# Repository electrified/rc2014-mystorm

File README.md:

## Board to interface 3.3v FPGA board with RC2014

BOM

5x SN74LVCC3245ADW

LD1117S33TR

100nF 0805 capacitors

10μF 0805 capacitors

OE low = enable
dir rc ->fpga

objcopy -Iihex -Obinary nascom32k_hexloadr.hex out.bin

sigrok-cli --driver saleae-logic16 --config samplerate=20Mhz --channels 0=D0,1=D1,2=D2,3=D3,4=D4,5=D5,6=D6,7=D7,9=RD,10=WR,11=MREQ,13=M1 --samples 1M --output-file z80-fpga

Silkscreen blunders

On the fpga connector, silscreen for M1 and RD should be swapped

https://bitbucket.org/gdevic/a-z80/src/6d6bd4838181ea9e088e6c1f7c68e4f11ce58183/host/basic_de1/basic_de1_fpga.sv?at=master&fileviewer=file-view-default

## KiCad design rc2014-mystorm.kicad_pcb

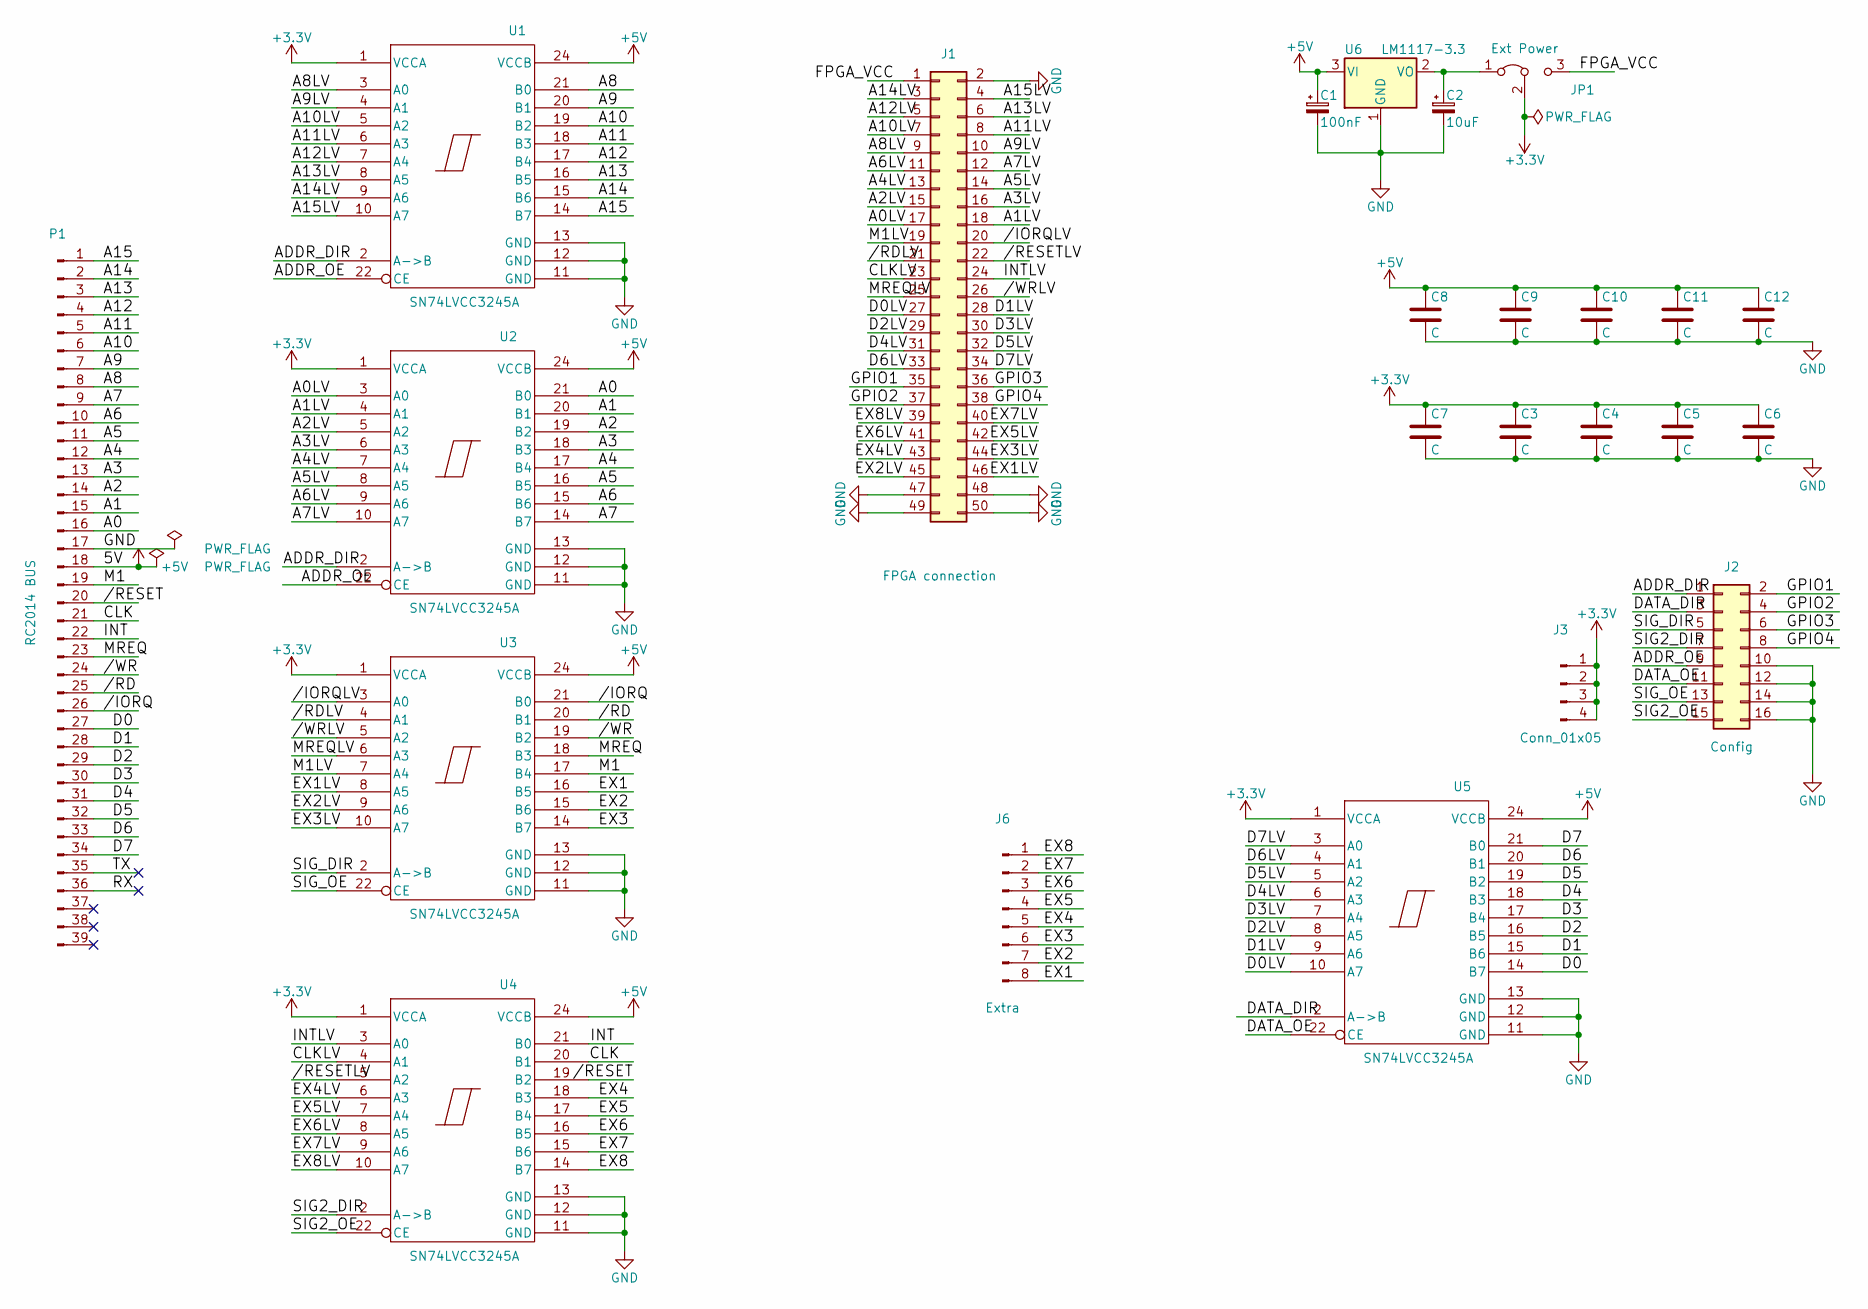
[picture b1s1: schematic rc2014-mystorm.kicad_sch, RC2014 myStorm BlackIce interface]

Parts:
C1: 100nF; C_0805_HandSoldering
C2: 10uF; C_0805_HandSoldering
C3, C4, C5, C6, C7, C8, C9, C10, C11, C12: C; C_0805_HandSoldering
J1: FPGA connection; IDC-Header_2x25_Pitch2.54mm_Straight
J2: Config; Pin_Header_Straight_2x08_Pitch2.54mm
J3: Conn_01x05; Pin_Header_Straight_1x04_Pitch2.54mm
J6: Extra; Pin_Header_Straight_1x08_Pitch2.54mm
JP1: Ext Power; Pin_Header_Straight_1x03_Pitch2.54mm
P1: RC2014 BUS; Pin_Header_Straight_1x39_Pitch2.54mm_NoSilk
U1, U2, U3, U4, U5: SN74LVCC3245A; SOIC-24W_7.5x15.4mm_Pitch1.27mm
U6: LM1117-3.3; SOT-223-3_TabPin2

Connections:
+3.3V: C3.1, C4.1, C5.1, C6.1, C7.1, J3.1, J3.2, J3.3, J3.4, JP1.2 (C), U1.1 (VCCA), U2.1 (VCCA), U3.1 (VCCA), U4.1 (VCCA), U5.1 (VCCA)
+5V: C1.1, C8.1, C9.1, C10.1, C11.1, C12.1, P1.18, U1.24 (VCCB), U2.24 (VCCB), U3.24 (VCCB), U4.24 (VCCB), U5.24 (VCCB), U6.3 (VI)
/A0: P1.16, U2.21 (B0)
/A0LV: J1.17, U2.3 (A0)
/A1: P1.15, U2.20 (B1)
/A1LV: J1.18, U2.4 (A1)
/A2: P1.14, U2.19 (B2)
/A2LV: J1.15, U2.5 (A2)
/A3: P1.13, U2.18 (B3)
/A3LV: J1.16, U2.6 (A3)
/A4: P1.12, U2.17 (B4)
/A4LV: J1.13, U2.7 (A4)
/A5: P1.11, U2.16 (B5)
/A5LV: J1.14, U2.8 (A5)
/A6: P1.10, U2.15 (B6)
/A6LV: J1.11, U2.9 (A6)
/A7: P1.9, U2.14 (B7)
/A7LV: J1.12, U2.10 (A7)
/A8: P1.8, U1.21 (B0)
/A8LV: J1.9, U1.3 (A0)
/A9: P1.7, U1.20 (B1)
/A9LV: J1.10, U1.4 (A1)
/A10: P1.6, U1.19 (B2)
/A10LV: J1.7, U1.5 (A2)
/A11: P1.5, U1.18 (B3)
/A11LV: J1.8, U1.6 (A3)
/A12: P1.4, U1.17 (B4)
/A12LV: J1.5, U1.7 (A4)
/A13: P1.3, U1.16 (B5)
/A13LV: J1.6, U1.8 (A5)
/A14: P1.2, U1.15 (B6)
/A14LV: J1.3, U1.9 (A6)
/A15: P1.1, U1.14 (B7)
/A15LV: J1.4, U1.10 (A7)
/ADDR_DIR: J2.1, U1.2 (A->B), U2.2 (A->B)
/ADDR_OE: J2.9, U1.22 (CE), U2.22 (CE)
/CLK: P1.21, U4.20 (B1)
/CLKLV: J1.23, U4.4 (A1)
/D0: P1.27, U5.14 (B7)
/D0LV: J1.27, U5.10 (A7)
/D1: P1.28, U5.15 (B6)
/D1LV: J1.28, U5.9 (A6)
/D2: P1.29, U5.16 (B5)
/D2LV: J1.29, U5.8 (A5)
/D3: P1.30, U5.17 (B4)
/D3LV: J1.30, U5.7 (A4)
/D4: P1.31, U5.18 (B3)
/D4LV: J1.31, U5.6 (A3)
/D5: P1.32, U5.19 (B2)
/D5LV: J1.32, U5.5 (A2)
/D6: P1.33, U5.20 (B1)
/D6LV: J1.33, U5.4 (A1)
/D7: P1.34, U5.21 (B0)
/D7LV: J1.34, U5.3 (A0)
/DATA_DIR: J2.3, U5.2 (A->B)
/DATA_OE: J2.11, U5.22 (CE)
/EX1: J6.8, U3.16 (B5)
/EX1LV: J1.46, U3.8 (A5)
/EX2: J6.7, U3.15 (B6)
/EX2LV: J1.45, U3.9 (A6)
/EX3: J6.6, U3.14 (B7)
/EX3LV: J1.44, U3.10 (A7)
/EX4: J6.5, U4.18 (B3)
/EX4LV: J1.43, U4.6 (A3)
/EX5: J6.4, U4.17 (B4)
/EX5LV: J1.42, U4.7 (A4)
/EX6: J6.3, U4.16 (B5)
/EX6LV: J1.41, U4.8 (A5)
/EX7: J6.2, U4.15 (B6)
/EX7LV: J1.40, U4.9 (A6)
/EX8: J6.1, U4.14 (B7)
/EX8LV: J1.39, U4.10 (A7)
/FPGA_VCC: J1.1, JP1.3 (B)
/GPIO1: J1.35, J2.2
/GPIO2: J1.37, J2.4
/GPIO3: J1.36, J2.6
/GPIO4: J1.38, J2.8
/INT: P1.22, U4.21 (B0)
/INTLV: J1.24, U4.3 (A0)
/M1: P1.19, U3.17 (B4)
/M1LV: J1.19, U3.7 (A4)
/MREQ: P1.23, U3.18 (B3)
/MREQLV: J1.25, U3.6 (A3)
/RX: P1.36
/SIG2_DIR: J2.7, U4.2 (A->B)
/SIG2_OE: J2.15, U4.22 (CE)
/SIG_DIR: J2.5, U3.2 (A->B)
/SIG_OE: J2.13, U3.22 (CE)
/TX: P1.35
//IORQ: P1.26, U3.21 (B0)
//IORQLV: J1.20, U3.3 (A0)
//RD: P1.25, U3.20 (B1)
//RDLV: J1.21, U3.4 (A1)
//RESET: P1.20, U4.19 (B2)
//RESETLV: J1.22, U4.5 (A2)
//WR: P1.24, U3.19 (B2)
//WRLV: J1.26, U3.5 (A2)
GND: C1.2, C2.2, C3.2, C4.2, C5.2, C6.2, C7.2, C8.2, C9.2, C10.2, C11.2, C12.2, J1.2, J1.47, J1.48, J1.49, J1.50, J2.10, J2.12, J2.14, J2.16, P1.17, U1.11 (GND), U1.12 (GND), U1.13 (GND), U2.11 (GND), U2.12 (GND), U2.13 (GND), U3.11 (GND), U3.12 (GND), U3.13 (GND), U4.11 (GND), U4.12 (GND), U4.13 (GND), U5.11 (GND), U5.12 (GND), U5.13 (GND), U6.1 (GND)
unnamed: C2.1, JP1.1 (A), U6.2 (VO)

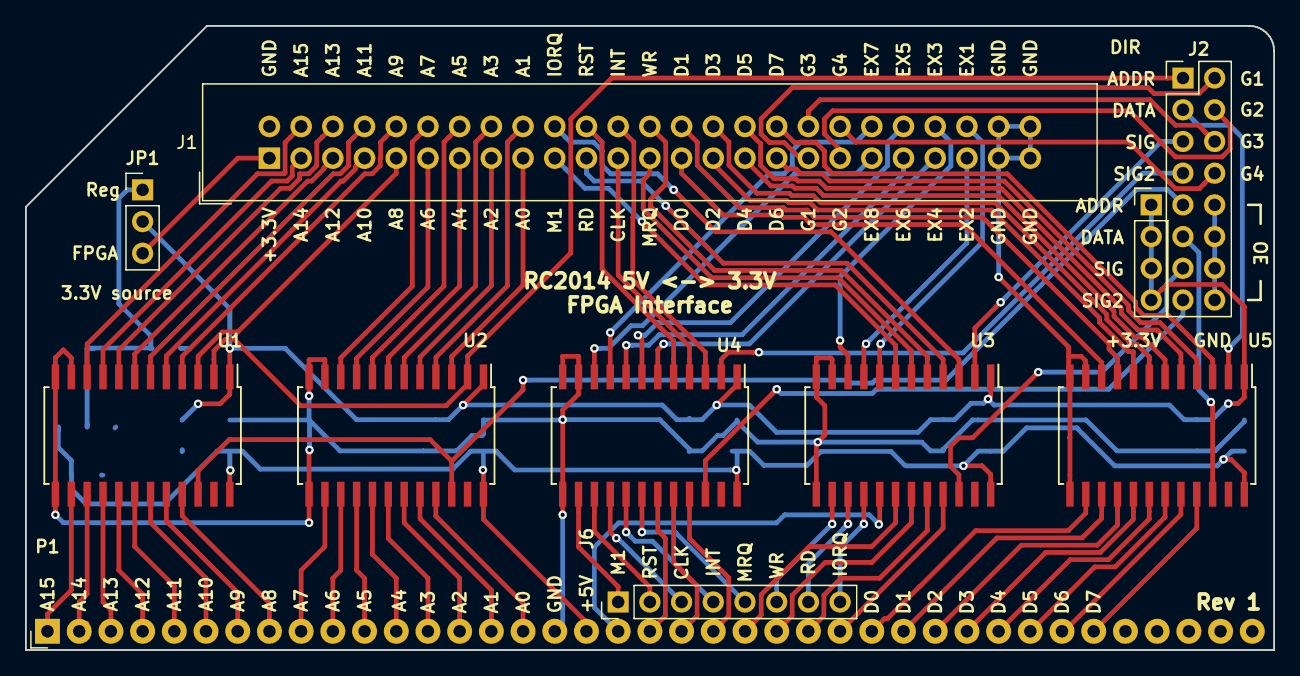
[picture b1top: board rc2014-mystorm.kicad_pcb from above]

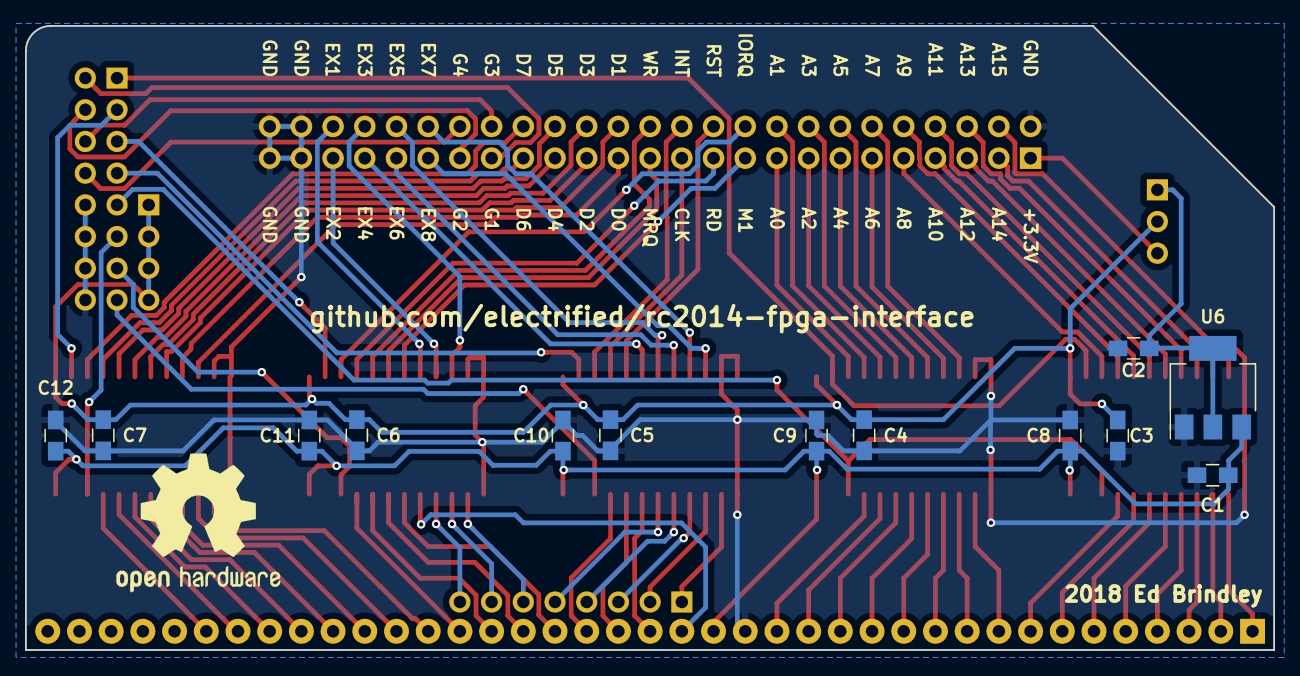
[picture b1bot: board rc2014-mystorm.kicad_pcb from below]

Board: 2 copper layers, 100.0 x 50.0 mm, 24 parts (13 on the bottom side), 97 nets.

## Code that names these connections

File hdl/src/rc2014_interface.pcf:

set_io LED1 71 #P52
#set_io LED2 67 #P53
#set_io LED3 #P54
#set_io LED4 #P55

set_io BUT1 63 #B1
set_io BUT2 64 #B1

set_io uart_tx 85 # rd0

#pmod 4
set_io A[14] 96 #P15
set_io A[12] 98 #P14
set_io A[10] 101 #P13
set_io A[8] 104 #P12

#pmod 3
set_io A[15] 97 #P11
set_io A[13] 99 #P10
set_io A[11] 102 #P9
set_io A[9] 105 #P8

#pmod 6
set_io A[6] 106 #P23
set_io A[4] 110 #P22
set_io A[2] 113 #P21
set_io A[0] 144 #P20

#pmod 5
set_io A[7] 107 #P19
set_io A[5] 112 #P18
set_io A[3] 114 #P17
set_io A[1] 143 #P16

#pmod 8
set_io M1 3 #P31
set_io RD 4 #P30
set_io CLK 7 #P29
set_io MRQ 8 #P28

#pmod 7
set_io IORQ 1 #P27
set_io RST 2 #P26
set_io INT 9 #P25
set_io WR 10 #P24

#pmod 10
set_io D[0] 11 #P39
set_io D[2] 12 #P38
set_io D[4] 17 #P37
set_io D[6] 18 #P36

#pmod 9
set_io D[1] 15 #P35
set_io D[3] 16 #P34
set_io D[5] 19 #P33
set_io D[7] 20 #P32

#pmod 12
set_io ADDR_DIR 25 #P47 #this is now data OE was ADDR_DIR
set_io DATA_DIR 26 #P46
#set_io EX7 31 #P45
#set_io EX[5] 32 #P44

#pmod 11
set_io SIG_DIR 21 #P43
set_io SIG2_DIR 22 #P42
#set_io EX[6] 33 #P41
#set_io EX[4] 34 #P40

#set_io EX[3]
#set_io EX[2]
#set_io EX[1]
#set_io EX[0]


# # SRAM
# set_io ADR[0] 137
# set_io ADR[1] 138
# set_io ADR[2] 139
# set_io ADR[3] 141
# set_io ADR[4] 142
# set_io ADR[5] 42
# set_io ADR[6] 43
# set_io ADR[7] 44
# set_io ADR[8] 73
# set_io ADR[9] 74
# set_io ADR[10] 75
# set_io ADR[11] 76
# set_io ADR[12] 115
# set_io ADR[13] 116
# set_io ADR[14] 117
# set_io ADR[15] 118
# set_io ADR[16] 119
# set_io ADR[17] 78
# #set_io ADR[18] 62

# set_io DAT[0] 135
# set_io DAT[1] 134
# set_io DAT[2] 130
# set_io DAT[3] 128
# set_io DAT[4] 125
# set_io DAT[5] 124
# set_io DAT[6] 122
# set_io DAT[7] 121
# #set_io DAT[8] 61
# #set_io DAT[9] 60
# #set_io DAT[10] 56
# #set_io DAT[11] 55
# #set_io DAT[12] 52
# #set_io DAT[13] 49
# #set_io DAT[14] 48
# #set_io DAT[15] 47

# set_io RAMOE_b 45
# set_io RAMWE_b 120
# set_io RAMCS_b 136

# Onboard 12Mhz oscillator
set_io fpga_clk 129

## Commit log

2017-09-18 realise layout blunder
2018-01-16 SMT....
2018-01-23 further SMT WIP
2018-02-10 Remove unused files and update readme
2018-02-19 gerbers as manuf'd and begginings of hdl
2018-03-09 hdl wip
2018-03-14 hdl wip..
2018-04-04 Fix PCB labels and more WIP
2019-05-01 upgrade to kicad 5, commit of hdl
2019-05-13 convert to nextpnr
2019-05-14 trying to get the serial output working
2026-01-03 resave with kicad 9 and tidy up - no attempt made to update to new component libraries
